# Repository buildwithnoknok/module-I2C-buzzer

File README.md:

# noknok Buzzer

A compact I²C‑controlled buzzer module for the noknok ecosystem.  
Designed for audio feedback, alerts, melodies, and UI interaction in modular builds.

> **Visual concept:** see [`docs/noknok-buzzer-concept.md`](docs/noknok-buzzer-concept.md) for the protocol and architecture diagram (Markdown + SVG, renders right here on GitHub). A styled interactive version is in [`docs/noknok-buzzer-concept.html`](docs/noknok-buzzer-concept.html) (open in a browser).

---

## Overview

The Buzzer Module uses a **CH32V003J4M6** microcontroller to drive an **MLT‑8530** magnetic buzzer via PWM through an MMBT3904 NPN transistor. It connects to the Raspberry Pi Pico (Conductor) over the standard noknok **JST SH 4‑pin I²C connector**.

The Conductor sends a short command — a frequency, duration, and volume, or just a tune ID — and the module handles everything else independently. The Pico is free to do other things while the buzzer plays.

---

## Features

- Dynamic I²C address via noknok enumeration protocol (no hardcoded address)
- CH32V003J4M6 microcontroller (RISC‑V, 48 MHz, 16 KB flash)
- Drives MLT‑8530 magnetic buzzer via PWM
- **Fire and forget** — all timing is handled on‑module
- **Volume control** (0–100%, maps to PWM duty cycle)
- **5 preloaded tunes** stored in flash (Nokia, Happy Birthday, Beep OK/Error, Startup Chime)
- Immediate interrupt — any new command stops whatever is playing
- 3.3V operation via noknok I²C connector
- Compact 20×20 mm PCB

---

## How It Works

```
Your Python code (Pico)          JST SH 4-pin           Buzzer Module (CH32V003)
────────────────────────         ────────────           ────────────────────────
                                  GND ────────
buzzer.play(440, 2.0)  ──────►   3.3V ───────  ──────►  receives 5 bytes
                                  SDA ─ data ─          sets PWM to 440 Hz
                                  SCL ─ clk  ─          starts 2s countdown
                                                         ← ACK (Pico moves on)
                                                         ... 2 seconds pass ...
                                                         timer fires → silence
```

The Pico sends **3–5 bytes** and returns immediately. The CH32V003 handles all timing internally using a hardware timer. No blocking, no waiting.

---

## I²C Protocol

**I²C address:** assigned dynamically at boot — see [Enumeration](#enumeration).

### Commands (Pico → Buzzer)

| Bytes | Command | Description |
|-------|---------|-------------|
| `0x00` | **STOP** | Silence immediately |
| `0x01` `fH` `fL` `dur` `vol` | **PLAY NOTE** | Play a tone |
| `0x02` `id` | **PLAY TUNE** | Play a preloaded tune |
| `0xB0` | **ENTER BOOTLOADER** | Reset into the I²C bootloader for an over‑the‑wire firmware update (see [Firmware](#firmware)) |
| `0xB1` | **GET VERSION** | Standard noknok command — the next read returns 4 version bytes (see below) |

**PLAY NOTE fields:**

| Field | Size | Description |
|-------|------|-------------|
| `fH` + `fL` | 2 bytes | Frequency in Hz, big‑endian (e.g. 440 Hz = `0x01 0xB8`) |
| `dur` | 1 byte | Duration in 100 ms units (1 = 100 ms, 10 = 1 s, 0 = play forever) |
| `vol` | 1 byte | Volume 0–100 |

### Status read (Pico ← Buzzer)

Read 1 byte from the module address:

| Value | Meaning |
|-------|---------|
| `0x01` | Currently playing |
| `0x00` | Idle |

### Version read (Pico ← Buzzer)

`GET_VERSION` (`0xB1`) is a **noknok ecosystem-standard** command (the `0xB0`–`0xBF` range is reserved for standard commands across every module). Write `0xB1`, then read **4 bytes**:

| Byte | Field | Meaning |
|------|-------|---------|
| 0 | `PROTOCOL_VERSION` | noknok protocol/API version the module speaks (`0x01`) |
| 1 | `FW_MAJOR` | Firmware major (`3`) |
| 2 | `FW_MINOR` | Firmware minor (`3`) |
| 3 | `FW_PATCH` | Firmware patch (`0`) |

Lets the Conductor compare the installed version against the version required by the product manifest. **→ Full spec:** [Ecosystem / software / readme.md §5](https://github.com/buildwithnoknok/Ecosystem/blob/main/software/readme.md#5-standard-system-commands)

---

## Preloaded Tunes

Tunes are stored as `const` arrays in the CH32V003's flash memory. Zero RAM cost.

| ID | Name | Notes |
|----|------|-------|
| `0x01` | Nokia Tune | 13 notes |
| `0x02` | Happy Birthday | 28 notes |
| `0x03` | Beep OK | Rising double beep |
| `0x04` | Beep Error | Low double buzz |
| `0x05` | Startup Chime | Rising 4‑note arpeggio (plays on every boot) |

---

## Enumeration

The module uses the standard noknok dynamic enumeration protocol — no hardcoded I²C address. At boot it plays the startup chime while counting a UID-derived backoff delay, then joins the bus at `0x7F` for address assignment by the Conductor.

**→ Full protocol spec:** [Ecosystem / software / enumeration.md](https://github.com/buildwithnoknok/Ecosystem/blob/main/software/enumeration.md)

---

## Python API

Use the `noknok.py` library from the [Ecosystem repo](https://github.com/buildwithnoknok/brain-Pico/tree/main/software) on the Pico.

```python
from noknok import Conductor

c = Conductor()        # GP8 = SDA, GP9 = SCL
c.enumerate()          # discover all modules (takes ~3 s)

# Single note — fire and forget
c.buzzer[0].play(440, 2000)             # 440 Hz for 2 seconds
c.buzzer[0].play(440, 1000, volume=50)  # half volume

# Predefined tune — fire and forget
c.buzzer[0].tune(c.buzzer[0].NOKIA)
c.buzzer[0].tune(c.buzzer[0].HAPPY_BIRTHDAY)
c.buzzer[0].tune(c.buzzer[0].BEEP_OK)

# Note in a melody — plays and waits
c.buzzer[0].note(440, 500)   # plays 440 Hz for 500 ms, then returns

# Stop
c.buzzer[0].stop()

# Status
c.buzzer[0].is_playing()     # True or False
c.buzzer[0].wait()           # block until idle

# Multiple buzzers
c.buzzer[1].play(880, 500)   # second buzzer (if present)
```

---

## Files on the Pico

These are **Conductor-level files shared by every module** - not buzzer-specific:

| File | Purpose |
|------|---------|
| `noknok.py` | noknok Conductor library - master copy in [brain-Pico/software](https://github.com/buildwithnoknok/brain-Pico/tree/main/software) |
| `noknok_state.json` | Module address persistence, auto-created by `enumerate()` - see [enumeration.md](https://github.com/buildwithnoknok/Ecosystem/blob/main/software/enumeration.md) |
| `noknok_roles.json` | Role -> UID mapping - see [roles.md](https://github.com/buildwithnoknok/Ecosystem/blob/main/software/roles.md) |

> **Filesystem write access required.** See the [CircuitPython filesystem docs](https://docs.circuitpython.org/en/latest/docs/library/storage.html).

---

## Hardware

| Spec | Value |
|------|-------|
| PCB size | 20 × 20 mm |
| MCU | CH32V003J4M6 (SOP‑8, RISC‑V, 48 MHz) |
| Buzzer | MLT‑8530 (magnetic, 3.3V) |
| Driver | MMBT3904 NPN transistor |
| Connector | JST SH 4‑pin (Qwiic / STEMMA QT compatible) |
| Supply voltage | 3.3V via I²C connector |
| PWM pin | PA1 (TIM1 CH2) |
| I²C SDA | PC1 |
| I²C SCL | PC2 |
| Flash header | J3 — 3-pad pogo (GND, SWIO, VCC), noknok M2.5-keyed footprint. SWIO/PD1 also carries the status LED (D3, active LOW). |
| Hardware version | v2.0 |

---

## Firmware

**v3.5.0 runs under the shared noknok I²C bootloader** ([module-I2C-bootloader](https://github.com/buildwithnoknok/module-I2C-bootloader)) — the module can be re‑flashed **over the I²C bus** (no SWDIO cable in the field). The application is linked at the `0x1400` offset (`app.ld`) above the 5 KB stage-0 + stage-1 bootloader (layout 2) and reserves the top 16 B of RAM for the bootloader handoff cell. Command `0xB0` drops the running module into the bootloader for an update.

```bash
cd firmware/src
make build   # compile the offset-linked application -> buzzer_firmware.bin
```

Flashing: normally over I²C from the Pico (`module_flasher.py` in `brain-Pico`). A blank board needs the bootloader SWD‑flashed once first. SWD remains the unbrickable backstop — see *Recovery & SWD flashing* in the [bootloader README](https://github.com/buildwithnoknok/module-I2C-bootloader#recovery--swd-flashing). `make flash` here still does a one‑off SWD flash of the app for bench bring‑up.

> ch32fun must be installed at `../ch32fun/` relative to `firmware/src/` — see [cnlohr/ch32v003fun](https://github.com/cnlohr/ch32v003fun) for setup instructions.

| Metric | Value |
|--------|-------|
| Firmware version | v3.5.0 (bootloader‑hosted) |
| Application size | 2928 B of 11 KB app region (26%) |
| RAM used | 76 B of ~2 KB (4%) |

### Files

| File | Description |
|------|-------------|
| `firmware/src/buzzer_firmware.c` | CH32V003 firmware source |
| `firmware/src/Makefile` | Build configuration |
| `firmware/src/funconfig.h` | ch32v003fun config |
| `firmware/src/app.ld` | Linker script (application at 0x1400, above the 1 KB stage-0 + 4 KB stage-1) |
| `firmware/bin/buzzer_firmware.bin` | Compiled application binary |
| `docs/noknok-buzzer-concept.md` | Concept diagram - Markdown + SVG (renders on GitHub) |
| `docs/noknok-buzzer-concept.html` | Same concept as a styled interactive page (browser) |

---

## Changelog

### v3.5.0 — app base 0x1400 (bootloader layout 2)
Relinked at the `0x1400` flash offset (bootloader **layout 2**: 1 KB stage-0 + 4 KB stage-1 below the app; was `0x1000`). Firmware behaviour unchanged. **Not compatible with the legacy monolithic bootloader or a layout-1 stage-1** — such a module gets stage-0 + stage-1 v1.1.0 over SWD first, then this app over I²C. See [module-I2C-bootloader](https://github.com/buildwithnoknok/module-I2C-bootloader).

### v3.4.0 — watchdog + boot-health handshake (DEV-31)
Runs the independent watchdog (~2 s, kicked every main-loop pass) and writes `0` to `0x200007F8` the moment its I²C address is assigned — the app-health handshake with the stage-1 bootloader. Stage-1 counts watchdog resets and parks the module (error 7, rescued by the Conductor by UID) after three in a row, instead of booting a broken app forever. Contract: [Ecosystem / software / bootloader-update.md §3](https://github.com/buildwithnoknok/Ecosystem/blob/main/software/bootloader-update.md). No protocol or command change.

### v3.3.1 and earlier
See the git history.

## Status

| Area | Status |
|------|--------|
| Hardware | v2.0 complete |
| Firmware | **v3.5.0 — complete (bootloader‑hosted, I²C OTA)** |
| Python library | **complete** (in [Ecosystem repo](https://github.com/buildwithnoknok/brain-Pico/tree/main/software)) |
| Documentation | **complete** |

---

## License

- Firmware / code: MIT — see [LICENSE](LICENSE).
- Hardware (schematics, PCB layout, fab files): CC BY-SA 4.0 — see [LICENSE-hardware](LICENSE-hardware).

## Trademarks

**noknok** is a registered trademark in Switzerland (Swissreg 1300007033).

Qwiic is a registered trademark of SparkFun Electronics, Inc. STEMMA QT is a
trademark of Adafruit Industries, LLC. Both are named here only to state
connector compatibility - noknok is not affiliated with, endorsed by, or
sponsored by either company.
---

---

## Safety & Liability

noknok hardware is an electronic device and a DIY/maker kit. You assemble, modify, flash, power, and operate it at your own risk, and it is provided as is, without warranty. See the full notice: [License, Safety & Liability](https://buildwithnoknok.github.io/safety-and-license/).

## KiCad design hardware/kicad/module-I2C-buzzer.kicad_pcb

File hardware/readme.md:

# Hardware — noknok Buzzer

Hardware design files for the noknok Buzzer module (CH32V003J4M6 — I2C-controlled magnetic buzzer).

- KiCad project: `kicad/module-I2C-buzzer.*`
- Schematic (PDF): `module-I2C-buzzer-Schematics.pdf`
- BOM: `module-I2C-buzzer_BOM.xls`
- Board renders: `module-I2C-buzzer-front.png`, `module-I2C-buzzer-back.png` *(pre-V2 renders — pending re-export)*

Hardware is licensed CC BY-SA 4.0 (see `../LICENSE-hardware`). Connector, flashing and mounting standards follow the [noknok Ecosystem guidelines](https://github.com/buildwithnoknok/Ecosystem) (electrical + mechanical).

---

## Hardware Change Record

### v2.0 — changes from v1.0
- **Fixed R1 (VDD series) to 1 Ω** — this was previously a documented-but-unfixed known issue: the schematic still shipped with the default 10 Ω, which caused a brownout reset when the buzzer fired at high volume (the beep current spike through 10 Ω trips BOR). V1 units needed a manual bodge; V2 corrects it in the schematic itself. This is a buzzer-specific deviation — knob and LED Button stay at the 10 Ω default (no spiky VDD load).
- **Status indicator LED on PD1** (in parallel with the SWIO flashing line — zero extra GPIO). Active-low: `+3V3_PROT → R2 (2.2 kΩ) → D3 anode; D3 cathode → PD1/SWIO`. Driven by the bootloader (off = app running, slow pulse = updating/recovering, solid = error). Parts: red 0603 LED (LCSC C2286) + 2.2 kΩ 0603 (LCSC C4190).
- **Removed both castellated edge pads** — the 5-pin flashing edge (old J4) and the redundant I2C edge (old J3). I2C is via the JST-SH (Qwiic) connectors J1/J2 only.
- **New flashing interface (J3)** — noknok flash pads (`noknok_FlashPads_I2C-module_1x3_M2.5`): 3 single-side SMD pogo pads (GND / SWIO / VCC) plus an embedded M2.5 keyed mounting hole, from the noknok KiCad library in the Ecosystem repo. Pad row is offset toward the keyed hole (not centered) so a 180°-flipped clamp contact can't seat and reverse-power the board.
- **Second mounting hole (H1)** — plain `noknok_MountingHole_2.5mm_M2.5`, diagonally opposite the flash-pad hole.
- **Removed the on-board I²C pull-up resistors** (previously R2/R3) — pull-ups now live on the host (Conductor), not per module (avoids stacking on the shared bus). The host must provide the bus pull-ups (proposed 3.3 kΩ); a noknok pull-up PCB covers third-party hosts that lack them. See the [I²C Pull-up Resistor Strategy ADR](https://noknokdev.atlassian.net/wiki/spaces/SD/pages/82280449). *(`R2` is reused above for the new status-LED resistor — it is not the old pull-up.)*
- **Buzzer drive resistor renumbered R4 → R3** (still 470 Ω, unchanged value) — a side effect of the old pull-ups' designators being freed up.
- D1 (protection Zener) and D2 (1N4148W) are unchanged from v1.0.

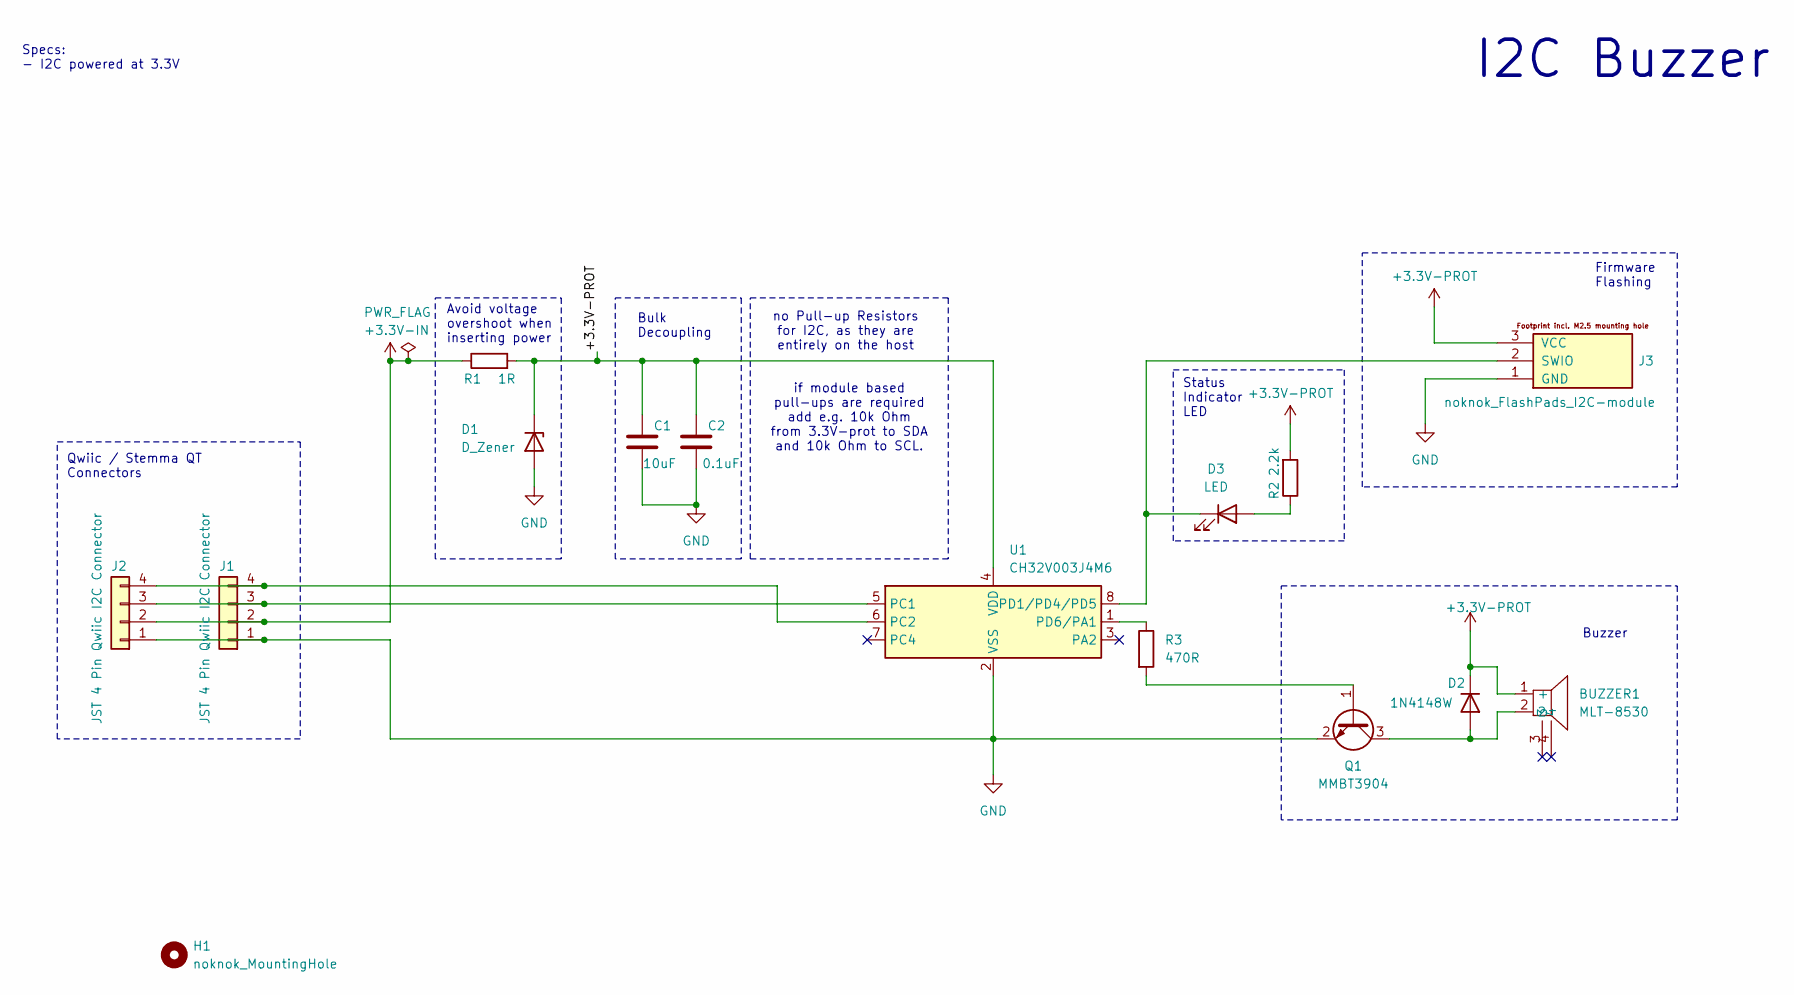
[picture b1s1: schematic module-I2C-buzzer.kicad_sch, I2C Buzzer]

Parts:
BUZZER1: MLT-8530; BUZ-SMD_4P-L8.5-W8.5-P8.50-BR; LCSC Part C94599
C1: 10uF; C_0603_1608Metric_Pad1.08x0.95mm_HandSolder
C2: 0.1uF; C_0603_1608Metric_Pad1.08x0.95mm_HandSolder
D1: D_Zener; D_SOD-323
D2: 1N4148W; D_SOD-123
D3: LED; LED_0603_1608Metric
H1: noknok_MountingHole; noknok_MountingHole_2.5mm_M2.5
J1, J2: JST 4 Pin Qwiic I2C Connector; JST_SH_SM04B-SRSS-TB_1x04-1MP_P1.00mm_Horizontal
J3: noknok_FlashPads_I2C-module; noknok_FlashPads_I2C-module_1x3_M2.5
Q1: MMBT3904; SOT-23
R1: 1R; R_0603_1608Metric
R2: 2.2k; R_0603_1608Metric
R3: 470R; R_0603_1608Metric_Pad0.98x0.95mm_HandSolder
U1: CH32V003J4M6; JEITA_SOIC-8_3.9x4.9mm_P1.27mm

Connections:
+3.3V-IN: J1.2, J2.2, R1.1
+3.3V-PROT: BUZZER1.1 (+), C1.1, C2.1, D1.1 (K), D2.1 (K), J3.3 (VCC), R1.2, R2.2, U1.4 (VDD)
GND: C1.2, C2.2, D1.2 (A), J1.1, J2.1, J3.1 (GND), Q1.2 (E), U1.2 (VSS)
unnamed: BUZZER1.2, D2.2 (A), Q1.3 (C)
unnamed: D3.2 (A), R2.1
unnamed: D3.1 (K), J3.2 (SWIO), U1.8 (PD1/PD4/PD5)
unnamed: J1.3, J2.3, U1.5 (PC1)
unnamed: J1.4, J2.4, U1.6 (PC2)
unnamed: Q1.1 (B), R3.2
unnamed: R3.1, U1.1 (PD6/PA1)

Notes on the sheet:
Specs: - I2C powered at 3.3V
Avoid voltage overshoot when inserting power
I2C Buzzer
no Pull-up Resistors for I2C, as they are entirely on the host
if module based pull-ups are required add e.g. 10k Ohm from 3.3V-prot to SDA and 10k Ohm to SCL.
Firmware Flashing
Buzzer
Status Indicator LED
Qwiic / Stemma QT Connectors
Bulk Decoupling

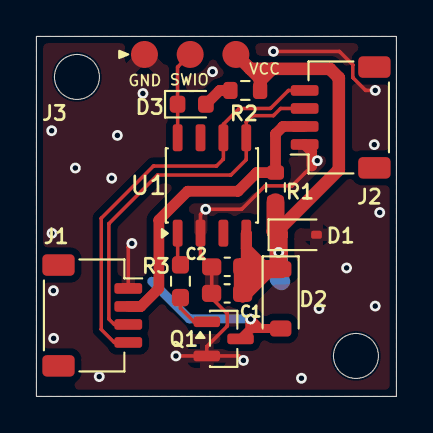
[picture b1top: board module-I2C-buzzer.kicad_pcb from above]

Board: 2 copper layers, 20.0 x 20.0 mm, 15 parts (1 on the bottom side), 10 nets.

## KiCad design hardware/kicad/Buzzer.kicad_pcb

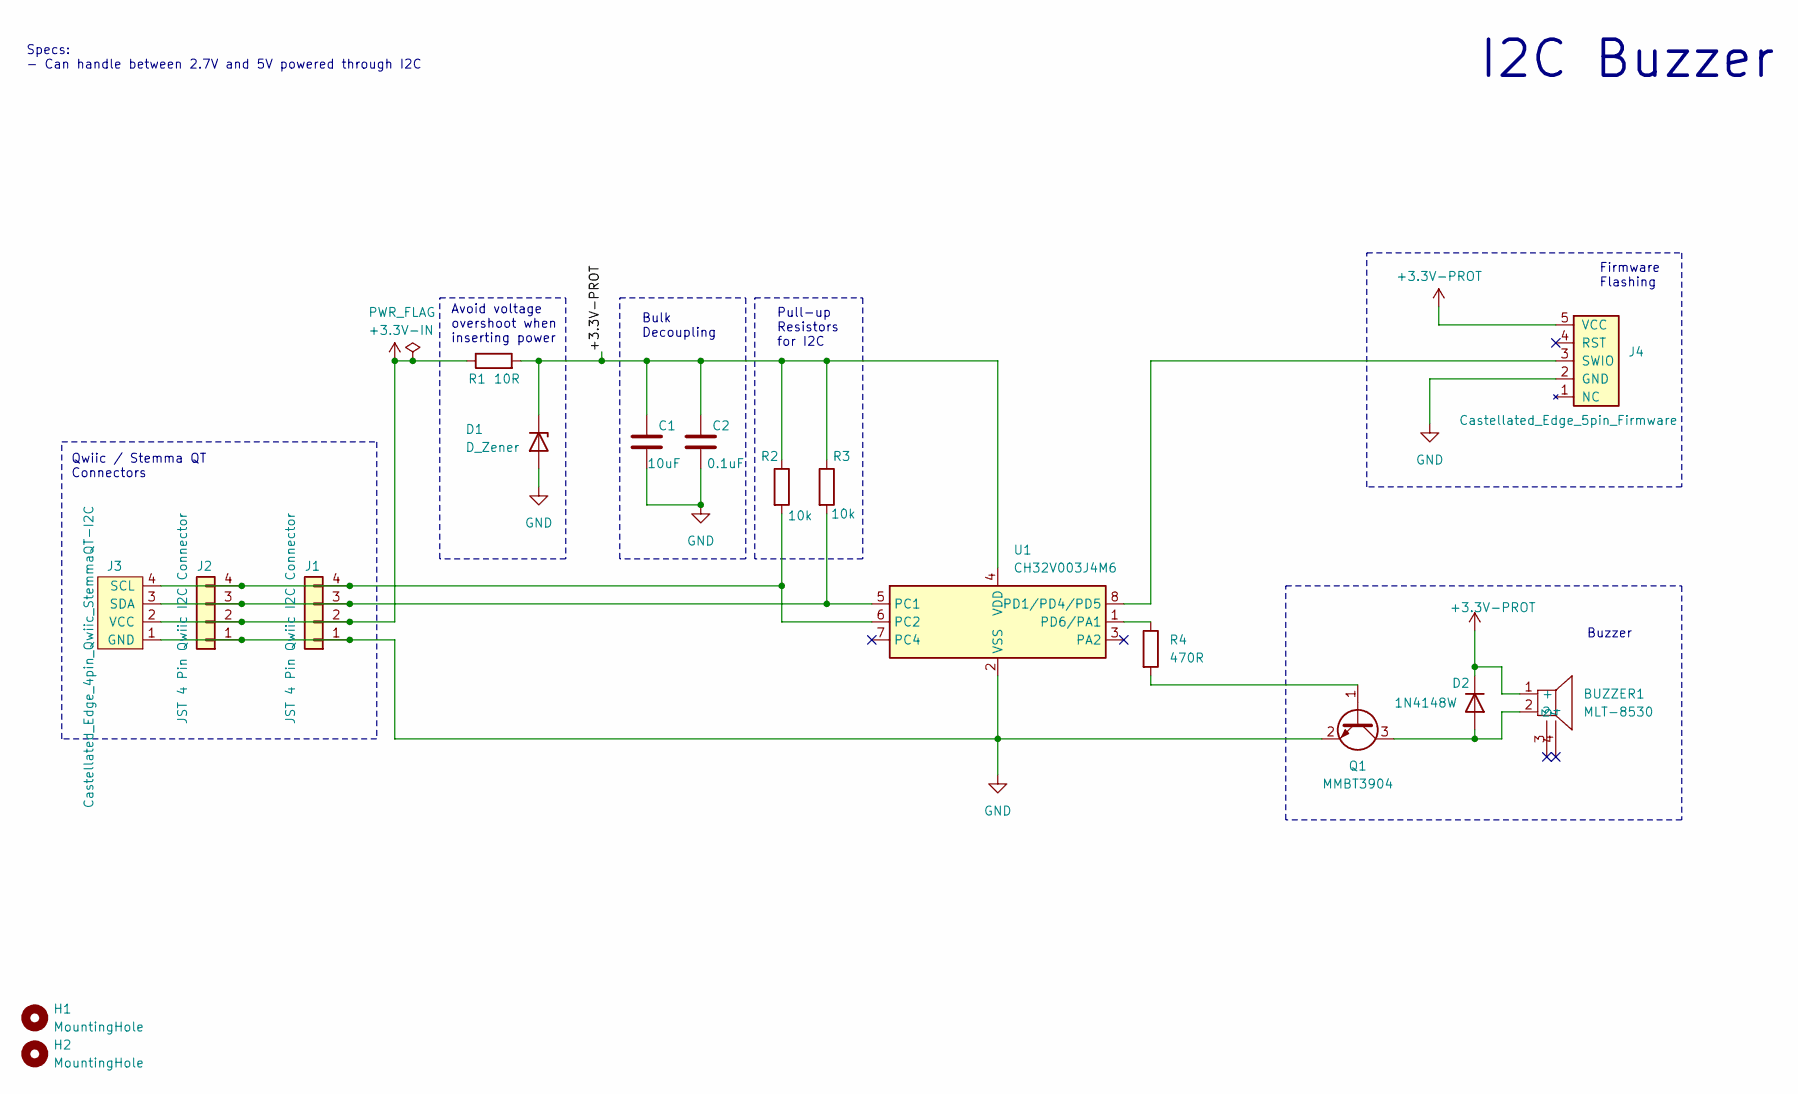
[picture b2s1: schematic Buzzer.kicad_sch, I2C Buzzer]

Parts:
BUZZER1: MLT-8530; BUZ-SMD_4P-L8.5-W8.5-P8.50-BR; LCSC Part C94599
C1: 10uF; C_0603_1608Metric_Pad1.08x0.95mm_HandSolder
C2: 0.1uF; C_0603_1608Metric_Pad1.08x0.95mm_HandSolder
D1: D_Zener; D_SOD-323
D2: 1N4148W; D_SOD-123
H1, H2: MountingHole; MountingHole_2.2mm_M2
J1, J2: JST 4 Pin Qwiic I2C Connector; JST_SH_SM04B-SRSS-TB_1x04-1MP_P1.00mm_Horizontal
J3: Castellated_Edge_4pin_Qwiic_StemmaQT-I2C; Castellated_edge_pad_I2C_4pin
J4: Castellated_Edge_5pin_Firmware; Castellated_edge_pad_Firmware
Q1: MMBT3904; SOT-23
R1: 10R; R_0603_1608Metric
R2, R3: 10k; R_0603_1608Metric_Pad0.98x0.95mm_HandSolder
R4: 470R; R_0603_1608Metric_Pad0.98x0.95mm_HandSolder
U1: CH32V003J4M6; JEITA_SOIC-8_3.9x4.9mm_P1.27mm

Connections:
+3.3V-IN: J1.2, J2.2, J3.2 (VCC), R1.1
+3.3V-PROT: BUZZER1.1 (+), C1.1, C2.1, D1.1 (K), D2.1 (K), J4.5 (VCC), R1.2, R2.1, R3.1, U1.4 (VDD)
GND: C1.2, C2.2, D1.2 (A), J1.1, J2.1, J3.1 (GND), J4.2 (GND), Q1.2 (E), U1.2 (VSS)
unnamed: BUZZER1.2, D2.2 (A), Q1.3 (C)
unnamed: J1.3, J2.3, J3.3 (SDA), R3.2, U1.5 (PC1)
unnamed: J1.4, J2.4, J3.4 (SCL), R2.2, U1.6 (PC2)
unnamed: J4.3 (SWIO), U1.8 (PD1/PD4/PD5)
unnamed: Q1.1 (B), R4.2
unnamed: R4.1, U1.1 (PD6/PA1)

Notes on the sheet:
Specs: - Can handle between 2.7V and 5V powered through I2C
Avoid voltage overshoot when inserting power
I2C Buzzer
Firmware Flashing
Buzzer
Qwiic / Stemma QT Connectors
Bulk Decoupling
Pull-up Resistors for I2C

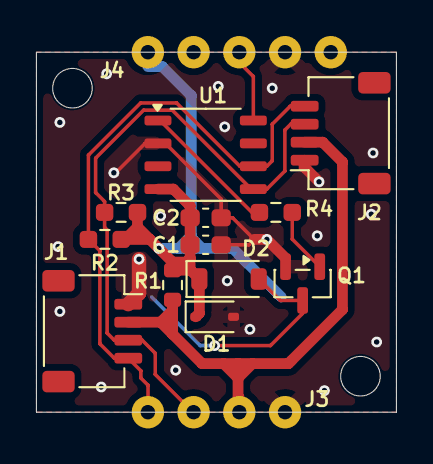
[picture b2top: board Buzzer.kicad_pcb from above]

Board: 2 copper layers, 20.0 x 20.0 mm, 17 parts (1 on the bottom side), 9 nets.

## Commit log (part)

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2026-05-08 Create hardware folder
2026-05-08 Create firmware folder
2026-05-08 Create docs folder
2026-05-08 Create hardware/kicad folder
2026-05-08 Upload schematics
2026-05-08 Add PCB images
2026-05-22 Initial working firmware & Python code for Pico
2026-06-01 Update product name to # noknok Buzzer
2026-06-01 fix: correct enumeration protocol comment (64-bit UID, 10-byte response)
2026-06-01 remove: delete noknok.py - single master copy lives in Ecosystem repo
2026-06-01 docs: update firmware version to v3.1, fix flash instructions, point noknok.py to Ecosystem repo
2026-06-01 docs: remove enumeration detail, link to Ecosystem/software/enumeration.md
2026-06-09 Add released firmware binary to firmware/bin
    Track the distributable offset-linked app image (flashed over I2C by the
    Pico). Adds a .gitignore exception so firmware/bin/*.bin is versioned while
    build artifacts elsewhere stay ignored.
2026-06-10 Remove noknok_enum_test.py from firmware/bin (moved to brain-Pico/software)
2026-06-10 Remove noknok_buzzer_test.py from firmware/bin (moved to brain-Pico/software)
2026-06-10 Remove Buzzer_OdeToTheJoy_Tune.py from firmware/bin (moved to brain-Pico/software)
2026-06-10 Remove noknok_setup_roles.py from firmware/bin (duplicate of brain-Pico/software)
2026-06-10 README: generic Pico files -> Conductor-level pointers (enumeration/roles); drop moved .py from Files table; fix noknok.py links to brain-Pico
2026-06-10 docs: add GitHub-readable Markdown version of the buzzer concept
2026-06-10 docs: add SVG concept diagram (GitHub-renderable)
2026-06-10 README: point concept link to the GitHub-readable Markdown (keep HTML for browser)
2026-06-10 firmware v3.3: add GET_VERSION (0xB1) standard command (DEV-1)
2026-06-10 Update released firmware binary for GET_VERSION (DEV-1)
2026-06-11 Add MIT + CC BY-SA 4.0 licenses and License/Safety README sections for public release
2026-06-11 firmware v3.3.1: version-only bump for OTA auto-update test (DEV-6)
    No functional change. Bumps FW_VERSION_PATCH 0->1 so installed 3.3.0
    buzzers see an installed-vs-required delta and exercise the OTA
    auto-update path once the manifest is pointed at 3.3.1 (Sue).
    Rebuilt offset-linked bin (2928 B, vector@0x1000).
2026-06-23 chore: remove redundant docs/.keep (folder now has content)
2026-06-23 chore: remove redundant hardware/.keep (folder now has content)
2026-06-23 chore: remove redundant hardware/kicad/.keep (folder now has content)
